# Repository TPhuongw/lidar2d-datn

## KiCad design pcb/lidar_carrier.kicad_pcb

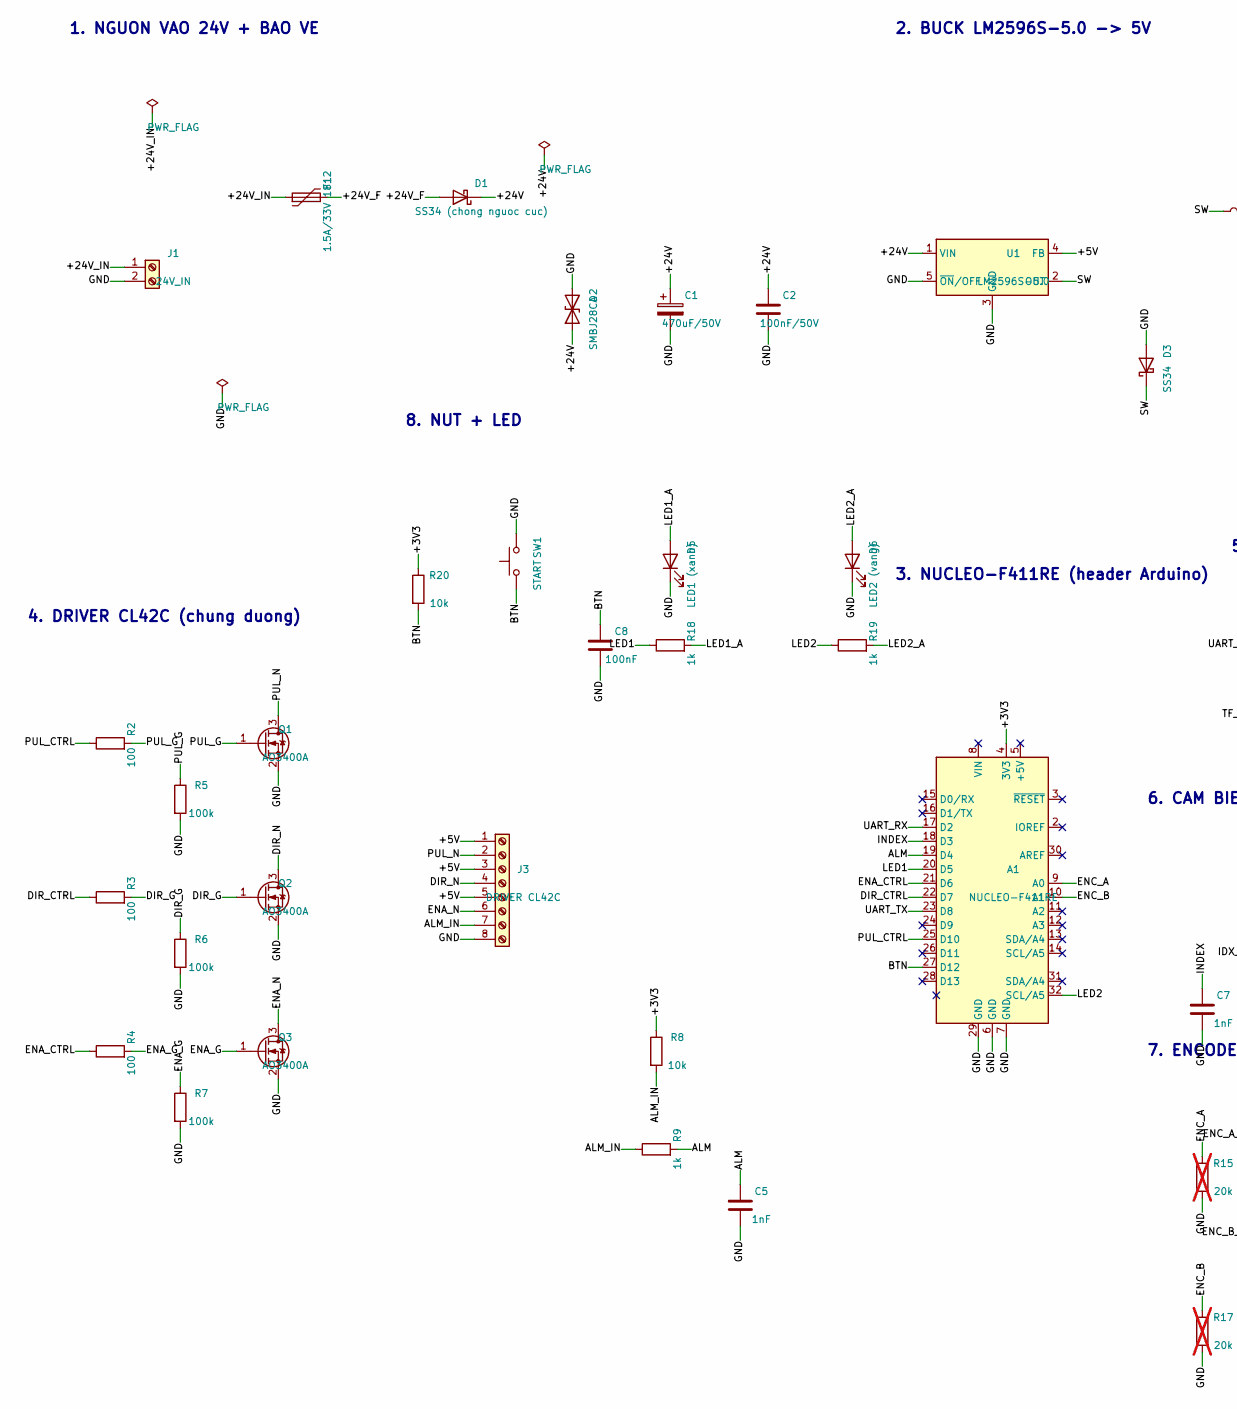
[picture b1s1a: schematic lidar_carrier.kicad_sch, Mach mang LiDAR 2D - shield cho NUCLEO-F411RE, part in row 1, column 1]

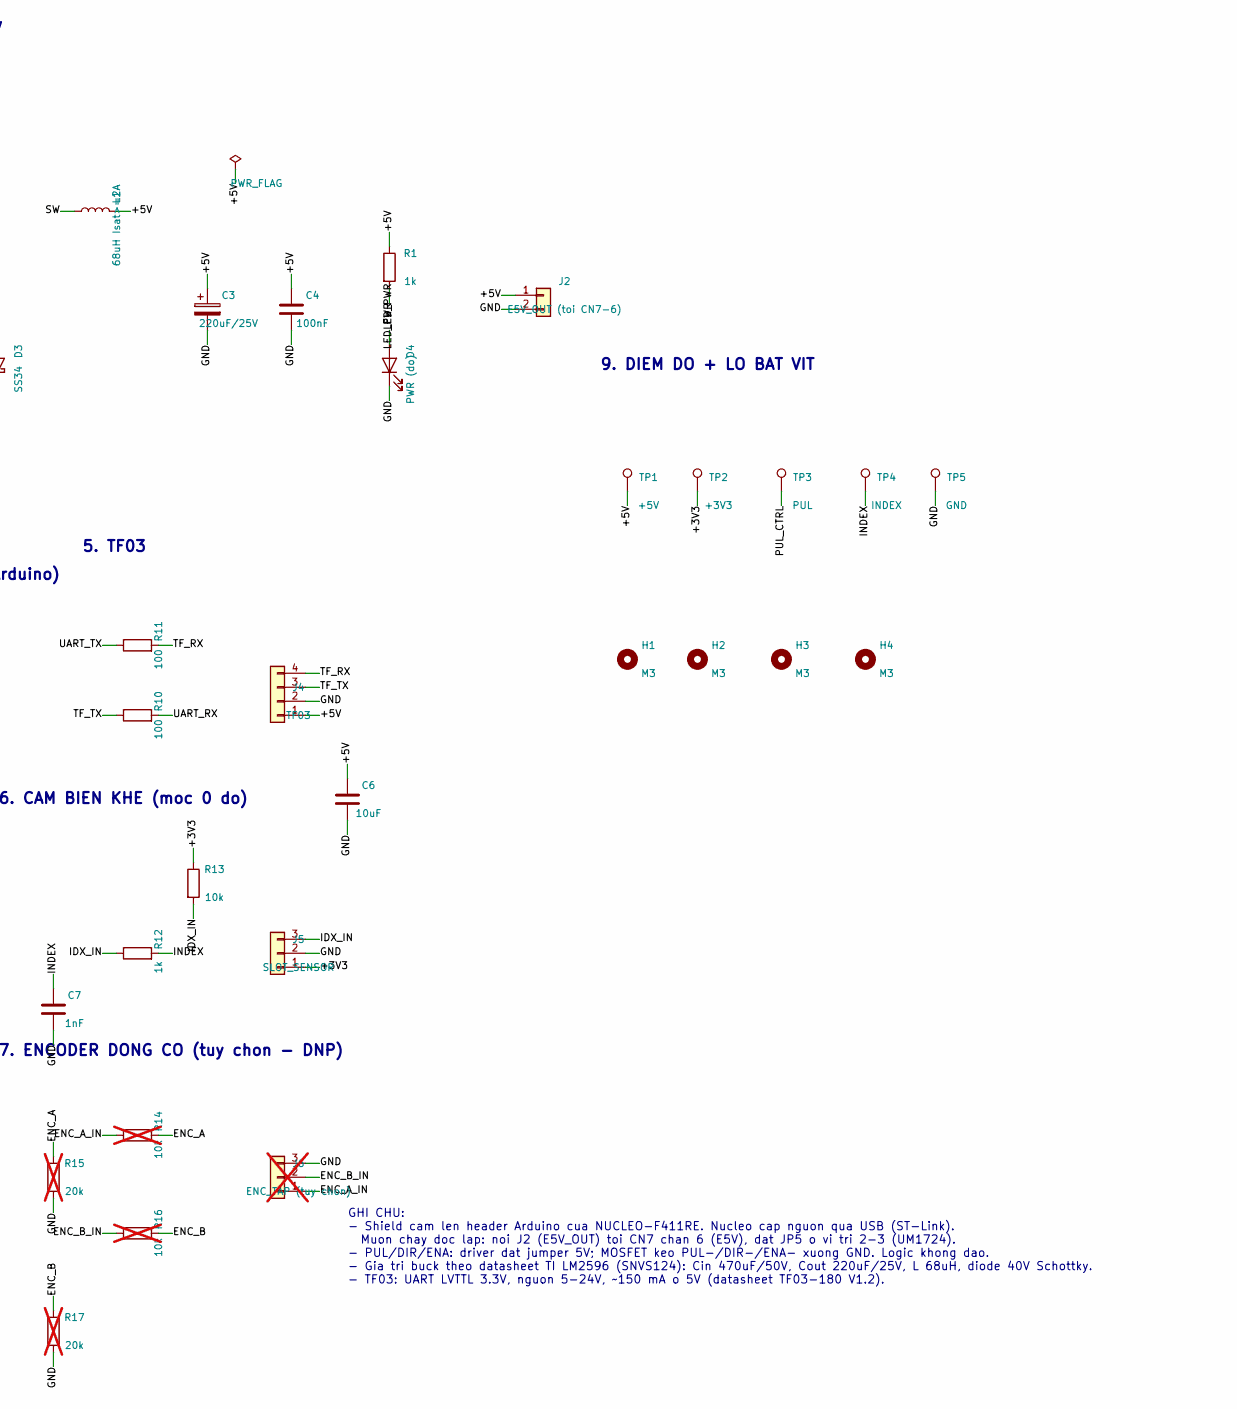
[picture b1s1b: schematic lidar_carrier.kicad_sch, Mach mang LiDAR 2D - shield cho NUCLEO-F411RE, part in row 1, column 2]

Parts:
A1: NUCLEO-F411RE; Arduino_UNO_R3
C1: 470uF/50V; CP_Radial_D10.0mm_P5.00mm
C2: 100nF/50V; C_0805_2012Metric_Pad1.18x1.45mm_HandSolder
C3: 220uF/25V; CP_Radial_D8.0mm_P3.50mm
C4, C8: 100nF; C_0805_2012Metric_Pad1.18x1.45mm_HandSolder
C5, C7: 1nF; C_0805_2012Metric_Pad1.18x1.45mm_HandSolder
C6: 10uF; C_0805_2012Metric_Pad1.18x1.45mm_HandSolder
D1: SS34 (chong nguoc cuc); D_SMA_Handsoldering
D2: SMBJ28CA; D_SMB_Handsoldering
D3: SS34; D_SMA_Handsoldering
D4: PWR (do); LED_0805_2012Metric_Pad1.15x1.40mm_HandSolder
D5: LED1 (xanh); LED_0805_2012Metric_Pad1.15x1.40mm_HandSolder
D6: LED2 (vang); LED_0805_2012Metric_Pad1.15x1.40mm_HandSolder
F1: 1.5A/33V 1812; Fuse_1812_4532Metric_Pad1.30x3.40mm_HandSolder
H1, H2, H3, H4: M3; MountingHole_3.2mm_M3
J1: 24V_IN; TerminalBlock_Phoenix_MKDS-1,5-2-5.08_1x02_P5.08mm_Horizont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
J2: E5V_OUT (toi CN7-6); PinHeader_1x02_P2.54mm_Vertical
J3: DRIVER CL42C; TerminalBlock_Phoenix_PT-1,5-8-3.5-H_1x08_P3.50mm_Horizontal
J4: TF03; JST_XH_B4B-XH-A_1x04_P2.50mm_Vertical
J5: SLOT_SENSOR; JST_XH_B3B-XH-A_1x03_P2.50mm_Vertical
J6: ENC_TAP (tuy chon); JST_XH_B3B-XH-A_1x03_P2.50mm_Vertical; not fitted
L1: 68uH Isat>=2A; L_12x12mm_H8mm
Q1, Q2, Q3: AO3400A; SOT-23
R1, R9, R12, R18, R19: 1k; R_0805_2012Metric_Pad1.20x1.40mm_HandSolder
R2, R3, R4, R10, R11: 100; R_0805_2012Metric_Pad1.20x1.40mm_HandSolder
R5, R6, R7: 100k; R_0805_2012Metric_Pad1.20x1.40mm_HandSolder
R8, R13, R20: 10k; R_0805_2012Metric_Pad1.20x1.40mm_HandSolder
R14, R16: 10k; R_0805_2012Metric_Pad1.20x1.40mm_HandSolder; not fitted
R15, R17: 20k; R_0805_2012Metric_Pad1.20x1.40mm_HandSolder; not fitted
SW1: START; SW_PUSH_6mm
TP1: +5V; TestPoint_Pad_D1.5mm
TP2: +3V3; TestPoint_Pad_D1.5mm
TP3: PUL; TestPoint_Pad_D1.5mm
TP4: INDEX; TestPoint_Pad_D1.5mm
TP5: GND; TestPoint_Pad_D1.5mm
U1: LM2596S-5.0; TO-263-5_TabPin3

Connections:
+3V3: A1.4 (3V3), J5.1, R8.1, R13.1, R20.1, TP2.1
+5V: C3.1, C4.1, C6.1, J2.1, J3.1, J3.3, J3.5, J4.1, L1.2, R1.1, TP1.1, U1.4 (FB)
+24V: C1.1, C2.1, D1.1 (K), D2.1 (A1), U1.1 (VIN)
+24V_F: D1.2 (A), F1.2
+24V_IN: F1.1, J1.1
ALM: A1.19 (D4), C5.1, R9.2
ALM_IN: J3.7, R8.2, R9.1
BTN: A1.27 (D12), C8.1, R20.2, SW1.1
DIR_CTRL: A1.22 (D7), R3.1
DIR_G: Q2.1 (G), R3.2, R6.1
DIR_N: J3.4, Q2.3 (D)
ENA_CTRL: A1.21 (D6), R4.1
ENA_G: Q3.1 (G), R4.2, R7.1
ENA_N: J3.6, Q3.3 (D)
ENC_A: A1.9 (A0), R14.2, R15.1
ENC_A_IN: J6.1, R14.1
ENC_B: A1.10 (A1), R16.2, R17.1
ENC_B_IN: J6.2, R16.1
GND: A1.6 (GND), A1.7 (GND), A1.29 (GND), C1.2, C2.2, C3.2, C4.2, C5.2, C6.2, C7.2, C8.2, D2.2 (A2), D3.2 (A), D4.1 (K), D5.1 (K), D6.1 (K), J1.2, J2.2, J3.8, J4.2, J5.2, J6.3, Q1.2 (S), Q2.2 (S), Q3.2 (S), R5.2, R6.2, R7.2, R15.2, R17.2, SW1.2, TP5.1, U1.3 (GND), U1.5 (~ON/OFF)
IDX_IN: J5.3, R12.1, R13.2
INDEX: A1.18 (D3), C7.1, R12.2, TP4.1
LED1: A1.20 (D5), R18.1
LED1_A: D5.2 (A), R18.2
LED2: A1.32 (SCL/A5), R19.1
LED2_A: D6.2 (A), R19.2
LED_PWR: D4.2 (A), R1.2
PUL_CTRL: A1.25 (D10), R2.1, TP3.1
PUL_G: Q1.1 (G), R2.2, R5.1
PUL_N: J3.2, Q1.3 (D)
SW: D3.1 (K), L1.1, U1.2 (OUT)
TF_RX: J4.4, R11.2
TF_TX: J4.3, R10.1
UART_RX: A1.17 (D2), R10.2
UART_TX: A1.23 (D8), R11.1

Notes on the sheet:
1. NGUON VAO 24V + BAO VE
2. BUCK LM2596S-5.0 -> 5V
3. NUCLEO-F411RE (header Arduino)
4. DRIVER CL42C (chung duong)
5. TF03
6. CAM BIEN KHE (moc 0 do)
7. ENCODER DONG CO (tuy chon - DNP)
8. NUT + LED
9. DIEM DO + LO BAT VIT
GHI CHU: - Shield cam len header Arduino cua NUCLEO-F411RE. Nucleo cap nguon qua USB (ST-Link). Muon chay doc lap: noi J2 (E5V_OUT) toi CN7 chan 6 (E5V), dat JP5 o vi tri 2-3 (UM1724). - PUL/DIR/ENA: driver dat jumper 5V; MOSFET keo PUL-/DIR-/ENA- xuong GND. Logic khong dao. - Gia tri buck theo dat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

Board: 2 copper layers, 57 parts (0 on the bottom side), 34 nets, no tracks yet.

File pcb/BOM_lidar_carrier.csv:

STT,Ref,Gia tri,Footprint,SL,Ghi chu
1,J1,24V_IN,"TerminalBlock_Phoenix_MKDS-1,5-2-5.08_1x02_P5.08mm_Horizontal",1,
2,F1,1.5A/33V 1812,Fuse_1812_4532Metric_Pad1.30x3.40mm_HandSolder,1,
3,D1,SS34 (chong nguoc cuc),D_SMA_Handsoldering,1,
4,D2,SMBJ28CA,D_SMB_Handsoldering,1,
5,C1,470uF/50V,CP_Radial_D10.0mm_P5.00mm,1,
6,C2,100nF/50V,C_0805_2012Metric_Pad1.18x1.45mm_HandSolder,1,
7,U1,LM2596S-5.0,TO-263-5_TabPin3,1,
8,D3,SS34,D_SMA_Handsoldering,1,
9,L1,68uH Isat>=2A,L_12x12mm_H8mm,1,
10,C3,220uF/25V,CP_Radial_D8.0mm_P3.50mm,1,
11,C4 C8,100nF,C_0805_2012Metric_Pad1.18x1.45mm_HandSolder,2,
12,R1 R9 R12 R18 R19,1k,R_0805_2012Metric_Pad1.20x1.40mm_HandSolder,5,
13,D4,PWR (do),LED_0805_2012Metric_Pad1.15x1.40mm_HandSolder,1,
14,J2,E5V_OUT (toi CN7-6),PinHeader_1x02_P2.54mm_Vertical,1,
15,A1,NUCLEO-F411RE,Arduino_UNO_R3,1,
16,Q1 Q2 Q3,AO3400A,SOT-23,3,
17,R2 R3 R4 R10 R11,100,R_0805_2012Metric_Pad1.20x1.40mm_HandSolder,5,
18,R5 R6 R7,100k,R_0805_2012Metric_Pad1.20x1.40mm_HandSolder,3,
19,J3,DRIVER CL42C,"TerminalBlock_Phoenix_PT-1,5-8-3.5-H_1x08_P3.50mm_Horizontal",1,
20,R8 R13 R14 R16 R20,10k,R_0805_2012Metric_Pad1.20x1.40mm_HandSolder,5,
21,C5 C7,1nF,C_0805_2012Metric_Pad1.18x1.45mm_HandSolder,2,
22,J4,TF03,JST_XH_B4B-XH-A_1x04_P2.50mm_Vertical,1,
23,C6,10uF,C_0805_2012Metric_Pad1.18x1.45mm_HandSolder,1,
24,J5,SLOT_SENSOR,JST_XH_B3B-XH-A_1x03_P2.50mm_Vertical,1,
25,J6,ENC_TAP (tuy chon),JST_XH_B3B-XH-A_1x03_P2.50mm_Vertical,1,DNP - chua lap
26,R15 R17,20k,R_0805_2012Metric_Pad1.20x1.40mm_HandSolder,2,DNP - chua lap
27,D5,LED1 (xanh),LED_0805_2012Metric_Pad1.15x1.40mm_HandSolder,1,
28,D6,LED2 (vang),LED_0805_2012Metric_Pad1.15x1.40mm_HandSolder,1,
29,SW1,START,SW_PUSH_6mm,1,

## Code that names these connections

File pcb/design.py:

"""
design.py - Nguon du lieu DUY NHAT cho mach mang LiDAR 2D (shield cam len NUCLEO-F411RE qua header Arduino).
Moi linh kien: ref, (thu vien, ky hieu), gia tri, footprint, vi tri tren so do (mm, luoi 2.54), xoay, {so chan: net}.
gen_sch.py va gen_pcb.py deu doc file nay -> so do va PCB luon khop nhau.

Phan chan Nucleo-F411RE (header Arduino, theo UM1724):
  D10=PB6 TIM4_CH1 -> PUL      D7=PA8  -> DIR        D6=PB10 -> ENA
  D4 =PB5 <- ALM (EXTI5)       D3=PB3 <- INDEX (EXTI3)
  D8 =PA9 USART1_TX -> TF03 RX D2=PA10 USART1_RX <- TF03 TX
  A0 =PA0 TIM2_CH1 <- ENC_A    A1=PA1 TIM2_CH2 <- ENC_B (tuy chon)
  D12=PA6 <- nut START (EXTI6) D5=PB4 -> LED1       D15=PB8 -> LED2
  D0/D1 (PA3/PA2) de trong: ST-Link VCP gui du lieu len PC.  D13 (PA5) = LED LD2 tren Nucleo.
"""

FP_R = "Resistor_SMD:R_0805_2012Metric_Pad1.20x1.40mm_HandSolder"
FP_C = "Capacitor_SMD:C_0805_2012Metric_Pad1.18x1.45mm_HandSolder"
FP_LED = "LED_SMD:LED_0805_2012Metric_Pad1.15x1.40mm_HandSolder"
FP_XH3 = "Connector_JST:JST_XH_B3B-XH-A_1x03_P2.50mm_Vertical"
FP_XH4 = "Connector_JST:JST_XH_B4B-XH-A_1x04_P2.50mm_Vertical"

R = ("Device", "R")
C = ("Device", "C")
CP = ("Device", "C_Polarized")
LED = ("Device", "LED")
DS = ("Device", "D_Schottky")

# (ref, symbol, value, footprint, x, y, rot, {pin: net})   - x,y la toa do tren so do (mm)
PARTS = [
    # ---------------- 1. Nguon vao 24 V + bao ve ----------------
    ("J1", ("Connector", "Screw_Terminal_01x02"), "24V_IN", "TerminalBlock_Phoenix:TerminalBlock_Phoenix_MKDS-1,5-2-5.08_1x02_P5.08mm_Horizontal",
     30.48, 50.8, 0, {"1": "+24V_IN", "2": "GND"}),
    ("F1", ("Device", "Polyfuse"), "1.5A/33V 1812", "Fuse:Fuse_1812_4532Metric_Pad1.30x3.40mm_HandSolder",
     50.8, 40.64, 90, {"1": "+24V_IN", "2": "+24V_F"}),
    ("D1", DS, "SS34 (chong nguoc cuc)", "Diode_SMD:D_SMA_Handsoldering",
     71.12, 40.64, 180, {"2": "+24V_F", "1": "+24V"}),
    ("D2", ("Device", "D_TVS"), "SMBJ28CA", "Diode_SMD:D_SMB_Handsoldering",
     86.36, 55.88, 90, {"1": "+24V", "2": "GND"}),
    ("C1", CP, "470uF/50V", "Capacitor_THT:CP_Radial_D10.0mm_P5.00mm",
     99.06, 55.88, 0, {"1": "+24V", "2": "GND"}),
    ("C2", C, "100nF/50V", FP_C, 111.76, 55.88, 0, {"1": "+24V", "2": "GND"}),

    # ---------------- 2. Buck LM2596S-5.0 (gia tri theo datasheet TI SNVS124) ----------------
    ("U1", ("Regulator_Switching", "LM2596S-5"), "LM2596S-5.0", "Package_TO_SOT_SMD:TO-263-5_TabPin3",
     139.7, 50.8, 0, {"1": "+24V", "2": "SW", "3": "GND", "4": "+5V", "5": "GND"}),
    ("D3", DS, "SS34", "Diode_SMD:D_SMA_Handsoldering",
     160.02, 63.5, 90, {"1": "SW", "2": "GND"}),
    ("L1", ("Device", "L"), "68uH Isat>=2A", "Inductor_SMD:L_12x12mm_H8mm",
     172.72, 43.18, 90, {"1": "SW", "2": "+5V"}),
    ("C3", CP, "220uF/25V", "Capacitor_THT:CP_Radial_D8.0mm_P3.50mm",
     187.96, 55.88, 0, {"1": "+5V", "2": "GND"}),
    ("C4", C, "100nF", FP_C, 198.12, 55.88, 0, {"1": "+5V", "2": "GND"}),
    ("R1", R, "1k", FP_R, 210.82, 50.8, 0, {"1": "+5V", "2": "LED_PWR"}),
    ("D4", LED, "PWR (do)", FP_LED, 210.82, 63.5, 90, {"2": "LED_PWR", "1": "GND"}),
    ("J2", ("Connector_Generic", "Conn_01x02"), "E5V_OUT (toi CN7-6)", "Connector_PinHeader_2.54mm:PinHeader_1x02_P2.54mm_Vertical",
     231.14, 53.34, 0, {"1": "+5V", "2": "GND"}),

    # ---------------- 3. Nucleo-F411RE (header Arduino) ----------------
    ("A1", ("MCU_Module", "Arduino_UNO_R3"), "NUCLEO-F411RE", "Module:Arduino_UNO_R3",
     139.7, 129.54, 0,
     {"17": "UART_RX", "18": "INDEX", "19": "ALM", "20": "LED1", "21": "ENA_CTRL", "22": "DIR_CTRL",
      "23": "UART_TX", "25": "PUL_CTRL", "27": "BTN", "9": "ENC_A", "10": "ENC_B", "32": "LED2",
      "4": "+3V3", "6": "GND", "7": "GND", "29": "GND",
      # chan khong dung (no-connect)
      "1": None, "2": None, "3": None, "5": None, "8": None, "11": None, "12": None, "13": None, "14": None,
      "15": None, "16": None, "24": None, "26": None, "28": None, "30": None, "31": None}),

    # ---------------- 4. Giao tiep driver CL42C (chung duong, MOSFET keo xuong) ----------------
    ("Q1", ("Transistor_FET", "AO3400A"), "AO3400A", "Package_TO_SOT_SMD:SOT-23",
     45.72, 111.76, 0, {"1": "PUL_G", "2": "GND", "3": "PUL_N"}),
    ("Q2", ("Transistor_FET", "AO3400A"), "AO3400A", "Package_TO_SOT_SMD:SOT-23",
     45.72, 132.08, 0, {"1": "DIR_G", "2": "GND", "3": "DIR_N"}),
    ("Q3", ("Transistor_FET", "AO3400A"), "AO3400A", "Package_TO_SOT_SMD:SOT-23",
     45.72, 152.4, 0, {"1": "ENA_G", "2": "GND", "3": "ENA_N"}),
    ("R2", R, "100", FP_R, 25.4, 111.76, 90, {"1": "PUL_CTRL", "2": "PUL_G"}),
    ("R3", R, "100", FP_R, 25.4, 132.08, 90, {"1": "DIR_CTRL", "2": "DIR_G"}),
    ("R4", R, "100", FP_R, 25.4, 152.4, 90, {"1": "ENA_CTRL", "2": "ENA_G"}),
    ("R5", R, "100k", FP_R, 35.56, 119.38, 0, {"1": "PUL_G", "2": "GND"}),
    ("R6", R, "100k", FP_R, 35.56, 139.7, 0, {"1": "DIR_G", "2": "GND"}),
    ("R7", R, "100k", FP_R, 35.56, 160.02, 0, {"1": "ENA_G", "2": "GND"}),
    ("J3", ("Connector", "Screw_Terminal_01x08"), "DRIVER CL42C", "TerminalBlock_Phoenix:TerminalBlock_Phoenix_PT-1,5-8-3.5-H_1x08_P3.50mm_Horizontal",
     76.2, 129.54, 0,
     {"1": "+5V", "2": "PUL_N", "3": "+5V", "4": "DIR_N", "5": "+5V", "6": "ENA_N", "7": "ALM_IN", "8": "GND"}),
    ("R8", R, "10k", FP_R, 96.52, 152.4, 0, {"1": "+3V3", "2": "ALM_IN"}),
    ("R9", R, "1k", FP_R, 96.52, 165.1, 90, {"1": "ALM_IN", "2": "ALM"}),
    ("C5", C, "1nF", FP_C, 106.68, 172.72, 0, {"1": "ALM", "2": "GND"}),

    # ---------------- 5. TF03 (UART LVTTL 3.3V, nguon 5V ~150 mA) ----------------
    ("J4", ("Connector_Generic", "Conn_01x04"), "TF03", FP_XH4,
     195.58, 106.68, 180, {"1": "+5V", "2": "GND", "3": "TF_TX", "4": "TF_RX"}),
    ("R10", R, "100", FP_R, 177.8, 109.22, 90, {"1": "TF_TX", "2": "UART_RX"}),
    ("R11", R, "100", FP_R, 177.8, 99.06, 90, {"1": "UART_TX", "2": "TF_RX"}),
    ("C6", C, "10uF", FP_C, 205.74, 119.38, 0, {"1": "+5V", "2": "GND"}),

    # ---------------- 6. Cam bien khe (moc 0 do) ----------------
    ("J5", ("Connector_Generic", "Conn_01x03"), "SLOT_SENSOR", FP_XH3,
     195.58, 139.7, 180, {"1": "+3V3", "2": "GND", "3": "IDX_IN"}),
    ("R12", R, "1k", FP_R, 177.8, 139.7, 90, {"1": "IDX_IN", "2": "INDEX"}),
    ("R13", R, "10k", FP_R, 185.42, 129.54, 0, {"1": "+3V3", "2": "IDX_IN"}),
    ("C7", C, "1nF", FP_C, 167.64, 147.32, 0, {"1": "INDEX", "2": "GND"}),

    # ---------------- 7. Encoder dong co (tuy chon, DNP) ----------------
    ("J6", ("Connector_Generic", "Conn_01x03"), "ENC_TAP (tuy chon)", FP_XH3,
     195.58, 167.64, 180, {"1": "ENC_A_IN", "2": "ENC_B_IN", "3": "GND"}),
    ("R14", R, "10k", FP_R, 177.8, 162.56, 90, {"1": "ENC_A_IN", "2": "ENC_A"}),
    ("R15", R, "20k", FP_R, 167.64, 167.64, 0, {"1": "ENC_A", "2": "GND"}),
    ("R16", R, "10k", FP_R, 177.8, 175.26, 90, {"1": "ENC_B_IN", "2": "ENC_B"}),
    ("R17", R, "20k", FP_R, 167.64, 187.96, 0, {"1": "ENC_B", "2": "GND"}),

    # ---------------- 8. Giao dien nguoi dung ----------------
    ("R18", R, "1k", FP_R, 99.06, 99.06, 90, {"1": "LED1", "2": "LED1_A"}),
    ("D5", LED, "LED1 (xanh)", FP_LED, 99.06, 88.9, 90, {"2": "LED1_A", "1": "GND"}),
    ("R19", R, "1k", FP_R, 121.92, 99.06, 90, {"1": "LED2", "2": "LED2_A"}),
    ("D6", LED, "LED2 (vang)", FP_LED, 121.92, 88.9, 90, {"2": "LED2_A", "1": "GND"}),
    ("SW1", ("Switch", "SW_Push"), "START", "Button_Switch_THT:SW_PUSH_6mm",
     78.74, 88.9, 90, {"1": "BTN", "2": "GND"}),
    ("R20", R, "10k", FP_R, 66.04, 91.44, 0, {"1": "+3V3", "2": "BTN"}),
    ("C8", C, "100nF", FP_C, 88.9, 99.06, 0, {"1": "BTN", "2": "GND"}),

    # ---------------- 9. Diem do + lo bat vit ----------------
    ("TP1", ("Connector", "TestPoint"), "+5V", "TestPoint:TestPoint_Pad_D1.5mm", 241.3, 78.74, 0, {"1": "+5V"}),
    ("TP2", ("Connector", "TestPoint"), "+3V3", "TestPoint:TestPoint_Pad_D1.5mm", 251.46, 78.74, 0, {"1": "+3V3"}),
    ("TP3", ("Connector", "TestPoint"), "PUL", "TestPoint:TestPoint_Pad_D1.5mm", 261.62, 78.74, 0, {"1": "PUL_CTRL"}),
    ("TP4", ("Connector", "TestPoint"), "INDEX", "TestPoint:TestPoint_Pad_D1.5mm", 271.78, 78.74, 0, {"1": "INDEX"}),
    ("TP5", ("Connector", "TestPoint"), "GND", "TestPoint:TestPoint_Pad_D1.5mm", 281.94, 78.74, 0, {"1": "GND"}),
    ("H1", ("Mechanical", "MountingHole"), "M3", "MountingHole:MountingHole_3.2mm_M3", 241.3, 101.6, 0, {}),
    ("H2", ("Mechanical", "MountingHole"), "M3", "MountingHole:MountingHole_3.2mm_M3", 251.46, 101.6, 0, {}),
    ("H3", ("Mechanical", "MountingHole"), "M3", "MountingHole:MountingHole_3.2mm_M3", 261.62, 101.6, 0, {}),
    ("H4", ("Mechanical", "MountingHole"), "M3", "MountingHole:MountingHole_3.2mm_M3", 271.78, 101.6, 0, {}),
]

# PWR_FLAG cho cac net nhan nguon tu dau noi (de ERC hieu net co nguon)
PWR_FLAGS = [("+24V_IN", 30.48, 30.48), ("GND", 40.64, 66.04), ("+24V", 81.28, 35.56), ("+5V", 190.5, 38.1)]

DNP = {"J6", "R14", "R15", "R16", "R17"}   # khu ma hoa encoder: lap sau neu can
